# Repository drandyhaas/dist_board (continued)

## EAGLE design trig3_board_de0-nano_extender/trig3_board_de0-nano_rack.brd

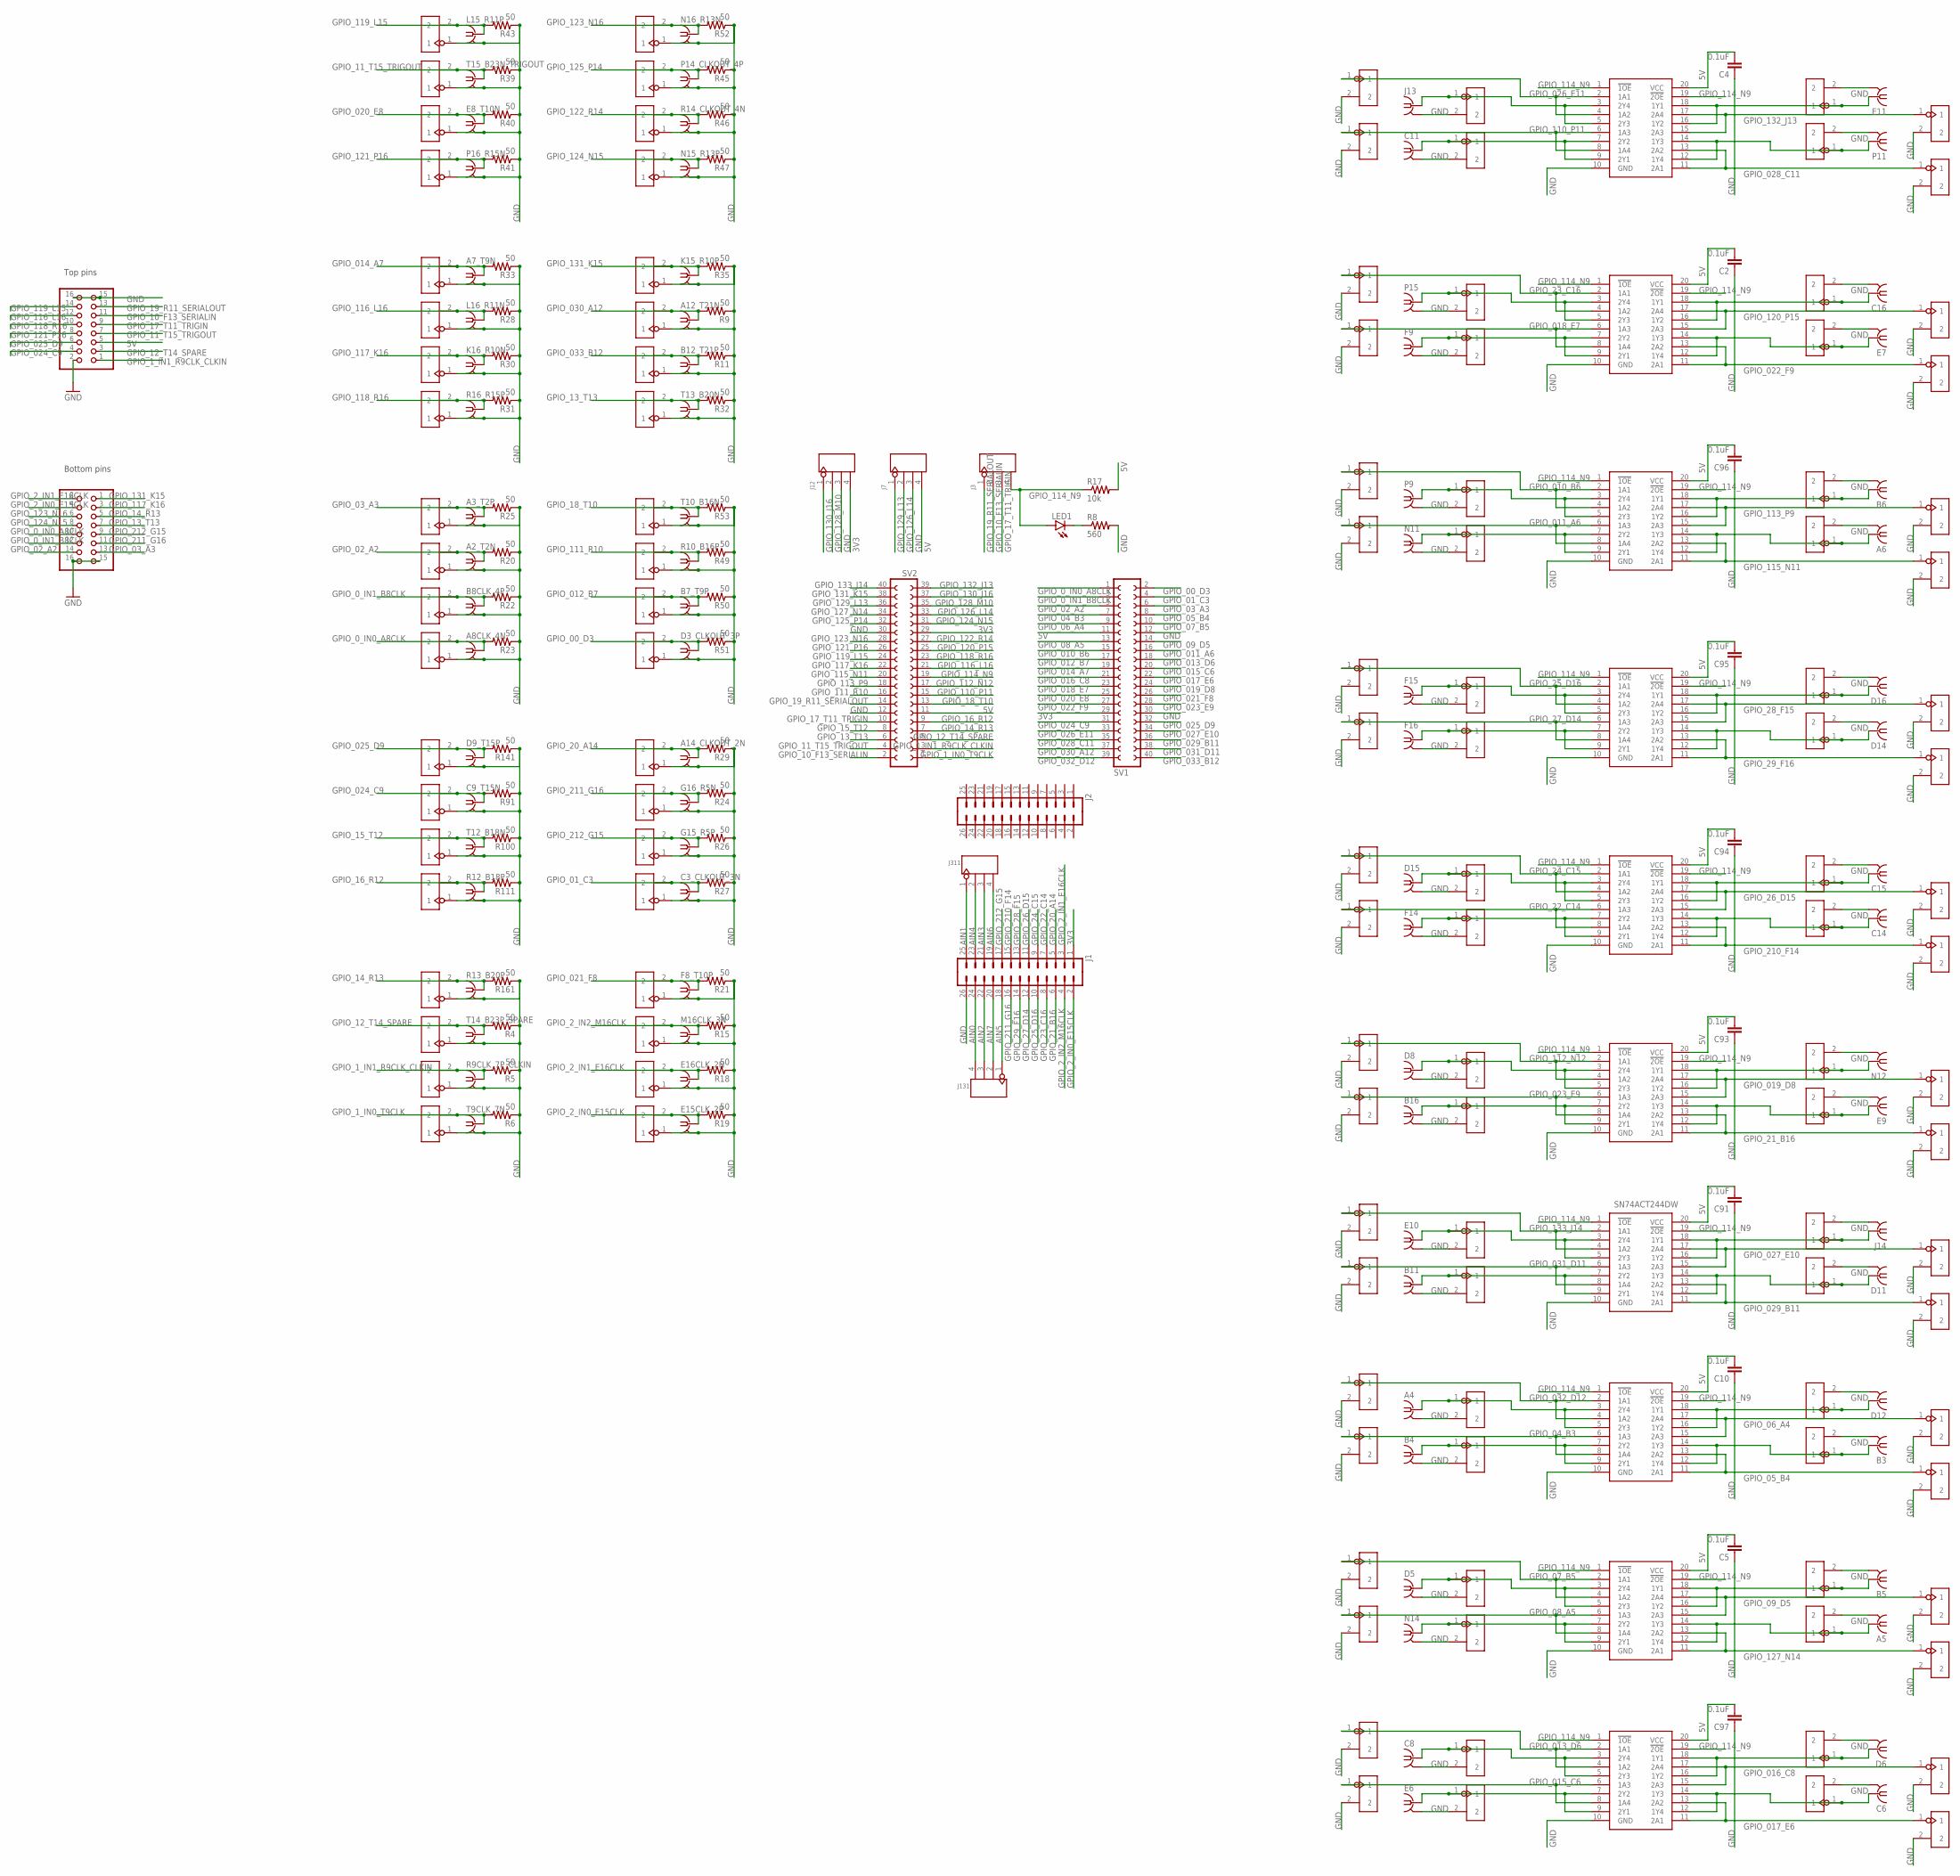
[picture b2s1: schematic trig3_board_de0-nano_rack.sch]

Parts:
A2_T2N, A3_T2P, A4, A5, A6, A7_T9N, A8CLK_4N, A12_T21N, A14_CLKOUT_2N: BU-SMB-V
B3, B4, B5, B6, B7_T9P, B8CLK_4P, B11, B12_T21P, B16: BU-SMB-V
C2, C4, C5, C10, C91, C93, C94, C95, C96, C97: 0.1uF; 0805
C3_CLKOUT_3N, C6, C8, C9_T15N, C11, C14, C15, C16: BU-SMB-V
D3_CLKOUT_3P, D5, D6, D8, D9_T15P, D11, D12, D14, D15, D16: BU-SMB-V
E6, E7, E8_T10N, E9, E10, E11, E15CLK_2P, E16CLK_2N: BU-SMB-V
F8_T10P, F9, F14, F15, F16: BU-SMB-V
G15_R5P, G16_R5N: BU-SMB-V
J1, J2: M13X22X13; 2X13
J3, J7, J12, J131, J311: 4p-2.54; H4-2.54
J4, J5, J6, J8, J9, J10, J11, J15, J16, J17, J18, J22, J23, J24, J25, J28, J29, J30, J31, J32, J33, J34, J35, J36, J37, J38, J39, J40, J41, J42, J43, J48, J49, J50, J51, J52, J53, J54, J55, J141: 2p-2.54; H2-2.54
J13, J14: BU-SMB-V
K15_R10P, K16_R10N: BU-SMB-V
L15_R11P, L16_R11N: BU-SMB-V
LED1: red; CHIP-LED0805
M16CLK_3N: BU-SMB-V
N11, N12, N14, N15_R13P, N16_R13N: BU-SMB-V
OJ1, OJ2, OJ3, OJ4, OJ5, OJ6, OJ7, OJ8, OJ17, OJ18, OJ19, OJ20, OJ21, OJ22, OJ23, OJ24, OJ25, OJ26, OJ27, OJ28, OJ29, OJ30, OJ31, OJ32, OJ33, OJ34, OJ35, OJ36, OJ37, OJ38, OJ39, OJ40, OJ41, OJ42, OJ43, OJ44, OJ45, OJ46, OJ47, OJ48, OJ49, OJ50, OJ51, OJ52, OJ53, OJ54, OJ55, OJ56, OJ57, OJ58, OJ59, OJ60, OJ61, OJ62, OJ63, OJ64, OJ65, OJ66, OJ67, OJ68, OJ69, OJ70, OJ71, OJ72, OJ73, OJ74, OJ75, OJ76, OJ77, OJ78, OJ79, OJ80, OJ89, OJ90, OJ91, OJ92, OJ93, OJ94, OJ95, OJ96: 2p-2.54; H2-2.54
P9, P11, P14_CLKOUT_4P, P15, P16_R15N: BU-SMB-V
PIN_AIN_PWRGND21: 15-91-2160; 2X08/90; MPN 15-91-2160
PIN_ANALOG_21: 15-91-2160; 2X08/90; MPN 15-91-2160
R4, R5, R6, R9, R11, R15, R18, R19, R20, R21, R22, R23, R24, R25, R26, R27, R28, R29, R30, R31, R32, R33, R35, R39, R40, R41, R43, R45, R46, R47, R49, R50, R51, R52, R53, R91, R100, R111, R141, R161: 50; AXIAL-0.3
R8: 560; R0805
R9CLK_7P_CLKIN, R10_B16P, R12_B18P, R13_B20P, R14_CLKOUT_4N, R16_R15P: BU-SMB-V
R17: 10k; R0805
SV1, SV2: FE20-2
T9CLK_7N, T10_B16N, T12_B18N, T13_B20N, T14_B23P_SPARE, T15_B23N_TRIGOUT: BU-SMB-V
VSLUE, VSLUE2, VSLUE3, VSLUE4, VSLUE5, VSLUE6, VSLUE7, VSLUE8, VSLUE9, VSLUE11: SN74ACT244DW; SOIC127P1030X265-20N

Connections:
3V3: J1.1, J12.4, SV1.29, SV2.29
5V: C2.2, C4.2, C5.2, C10.2, C91.2, C93.2, C94.2, C95.2, C96.2, C97.2, J7.4, PIN_ANALOG_21.5, R17.2, SV1.11, SV2.11, VSLUE.20 (VCC), VSLUE2.20 (VCC), VSLUE3.20 (VCC), VSLUE4.20 (VCC), VSLUE5.20 (VCC), VSLUE6.20 (VCC), VSLUE7.20 (VCC), VSLUE8.20 (VCC), VSLUE9.20 (VCC), VSLUE11.20 (VCC)
AIN0: J1.24, J131.4
AIN1: J1.25, J311.1
AIN2: J1.22, J131.3
AIN3: J1.21, J311.3
AIN4: J1.23, J311.2
AIN5: J1.18, J131.1
AIN6: J1.19, J311.4
AIN7: J1.20, J131.2
GND: A2_T2N.2, A2_T2N.3 (2), A2_T2N.4 (2), A2_T2N.5 (2), A3_T2P.2, A3_T2P.3 (2), A3_T2P.4 (2), A3_T2P.5 (2), A4.2, A4.3 (2), A4.4 (2), A4.5 (2), A5.2, A5.3 (2), A5.4 (2), A5.5 (2), A6.2, A6.3 (2), A6.4 (2), A6.5 (2), A7_T9N.2, A7_T9N.3 (2), A7_T9N.4 (2), A7_T9N.5 (2), A8CLK_4N.2, A8CLK_4N.3 (2), A8CLK_4N.4 (2), A8CLK_4N.5 (2), A12_T21N.2, A12_T21N.3 (2), A12_T21N.4 (2), A12_T21N.5 (2), A14_CLKOUT_2N.2, A14_CLKOUT_2N.3 (2), A14_CLKOUT_2N.4 (2), A14_CLKOUT_2N.5 (2), B3.2, B3.3 (2), B3.4 (2), B3.5 (2), B4.2, B4.3 (2), B4.4 (2), B4.5 (2), B5.2, B5.3 (2), B5.4 (2), B5.5 (2), B6.2, B6.3 (2), B6.4 (2), B6.5 (2), B7_T9P.2, B7_T9P.3 (2), B7_T9P.4 (2), B7_T9P.5 (2), B8CLK_4P.2, B8CLK_4P.3 (2), B8CLK_4P.4 (2), B8CLK_4P.5 (2), B11.2, B11.3 (2), B11.4 (2), B11.5 (2), B12_T21P.2, B12_T21P.3 (2), B12_T21P.4 (2), B12_T21P.5 (2), B16.2, B16.3 (2), B16.4 (2), B16.5 (2), C2.1, C3_CLKOUT_3N.2, C3_CLKOUT_3N.3 (2), C3_CLKOUT_3N.4 (2), C3_CLKOUT_3N.5 (2), C4.1, C5.1, C6.2, C6.3 (2), C6.4 (2), C6.5 (2), C8.2, C8.3 (2), C8.4 (2), C8.5 (2), C9_T15N.2, C9_T15N.3 (2), C9_T15N.4 (2), C9_T15N.5 (2), C10.1, C11.2, C11.3 (2), C11.4 (2), C11.5 (2), C14.2, C14.3 (2), C14.4 (2), C14.5 (2), C15.2, C15.3 (2), C15.4 (2), C15.5 (2), C16.2, C16.3 (2), C16.4 (2), C16.5 (2), C91.1, C93.1, C94.1, C95.1, C96.1, C97.1, D3_CLKOUT_3P.2, D3_CLKOUT_3P.3 (2), D3_CLKOUT_3P.4 (2), D3_CLKOUT_3P.5 (2), D5.2, D5.3 (2), D5.4 (2), D5.5 (2), D6.2, D6.3 (2), D6.4 (2), D6.5 (2), D8.2, D8.3 (2), D8.4 (2), D8.5 (2), D9_T15P.2, D9_T15P.3 (2), D9_T15P.4 (2), D9_T15P.5 (2), D11.2, D11.3 (2), D11.4 (2), D11.5 (2), D12.2, D12.3 (2), D12.4 (2), D12.5 (2), D14.2, D14.3 (2), D14.4 (2), D14.5 (2), D15.2, D15.3 (2), D15.4 (2), D15.5 (2), D16.2, D16.3 (2), D16.4 (2), D16.5 (2), E6.2, E6.3 (2), E6.4 (2), E6.5 (2), E7.2, E7.3 (2), E7.4 (2), E7.5 (2), E8_T10N.2, E8_T10N.3 (2), E8_T10N.4 (2), E8_T10N.5 (2), E9.2, E9.3 (2), E9.4 (2), E9.5 (2), E10.2, E10.3 (2), E10.4 (2), E10.5 (2), E11.2, E11.3 (2), E11.4 (2), E11.5 (2), E15CLK_2P.2, E15CLK_2P.3 (2), E15CLK_2P.4 (2), E15CLK_2P.5 (2), E16CLK_2N.2, E16CLK_2N.3 (2), E16CLK_2N.4 (2), E16CLK_2N.5 (2), F8_T10P.2, F8_T10P.3 (2), F8_T10P.4 (2), F8_T10P.5 (2), F9.2, F9.3 (2), F9.4 (2), F9.5 (2), F14.2, F14.3 (2), F14.4 (2), F14.5 (2), F15.2, F15.3 (2), F15.4 (2), F15.5 (2), F16.2, F16.3 (2), F16.4 (2), F16.5 (2), G15_R5P.2, G15_R5P.3 (2), G15_R5P.4 (2), G15_R5P.5 (2), G16_R5N.2, G16_R5N.3 (2), G16_R5N.4 (2), G16_R5N.5 (2), J1.26, J4.1, J5.1, J6.1, J7.3, J8.1, J9.1, J10.1, J11.1, J12.3, J13.2, J13.3 (2), J13.4 (2), J13.5 (2), J14.2, J14.3 (2), J14.4 (2), J14.5 (2), J15.1, J16.1, J17.1, J18.1, J22.1, J23.1, J24.1, J25.1, J28.1, J29.1, J30.1, J31.1, J32.1, J33.1, J34.1, J35.1, J36.1, J37.1, J38.1, J39.1, J40.1, J41.1, J42.1, J43.1, J48.1, J49.1, J50.1, J51.1, J52.1, J53.1, J54.1, J55.1, J141.1, K15_R10P.2, K15_R10P.3 (2), K15_R10P.4 (2), K15_R10P.5 (2), K16_R10N.2, K16_R10N.3 (2), K16_R10N.4 (2), K16_R10N.5 (2), L15_R11P.2, L15_R11P.3 (2), L15_R11P.4 (2), L15_R11P.5 (2), L16_R11N.2, L16_R11N.3 (2), L16_R11N.4 (2), L16_R11N.5 (2), M16CLK_3N.2, M16CLK_3N.3 (2), M16CLK_3N.4 (2), M16CLK_3N.5 (2), N11.2, N11.3 (2), N11.4 (2), N11.5 (2), N12.2, N12.3 (2), N12.4 (2), N12.5 (2), N14.2, N14.3 (2), N14.4 (2), N14.5 (2), N15_R13P.2, N15_R13P.3 (2), N15_R13P.4 (2), N15_R13P.5 (2), N16_R13N.2, N16_R13N.3 (2), N16_R13N.4 (2), N16_R13N.5 (2), OJ1.2, OJ2.2, OJ3.2, OJ4.2, OJ5.2, OJ6.2, OJ7.2, OJ8.2, OJ17.2, OJ18.2, OJ19.2, OJ20.2, OJ21.2, OJ22.2, OJ23.2, OJ24.2, OJ25.2, OJ26.2, OJ27.2, OJ28.2, OJ29.2, OJ30.2, OJ31.2, OJ32.2, OJ33.2, OJ34.2, OJ35.2, OJ36.2, OJ37.2, OJ38.2, OJ39.2, OJ40.2, OJ41.2, OJ42.2, OJ43.2, OJ44.2, OJ45.2, OJ46.2, OJ47.2, OJ48.2, OJ49.2, OJ50.2, OJ51.2, OJ52.2, OJ53.2, OJ54.2, OJ55.2, OJ56.2, OJ57.2, OJ58.2, OJ59.2, OJ60.2, OJ61.2, OJ62.2, OJ63.2, OJ64.2, OJ65.2, OJ66.2, OJ67.2, OJ68.2, OJ69.2, OJ70.2, OJ71.2, OJ72.2, OJ73.2, OJ74.2, OJ75.2, OJ76.2, OJ77.2, OJ78.2, OJ79.2, OJ80.2, OJ89.2, OJ90.2, OJ91.2, OJ92.2, OJ93.2, OJ94.2, OJ95.2, OJ96.2, P9.2, P9.3 (2), P9.4 (2), P9.5 (2), P11.2, P11.3 (2), P11.4 (2), P11.5 (2), P14_CLKOUT_4P.2, P14_CLKOUT_4P.3 (2), P14_CLKOUT_4P.4 (2), P14_CLKOUT_4P.5 (2), P15.2, P15.3 (2), P15.4 (2), P15.5 (2), P16_R15N.2, P16_R15N.3 (2), P16_R15N.4 (2), P16_R15N.5 (2), PIN_AIN_PWRGND21.15, PIN_AIN_PWRGND21.16, PIN_ANALOG_21.2, PIN_ANALOG_21.15, PIN_ANALOG_21.16, R4.P$1 (1), R5.P$1 (1), R6.P$1 (1), R8.2, R9.P$1 (1), R9CLK_7P_CLKIN.2, R9CLK_7P_CLKIN.3 (2), R9CLK_7P_CLKIN.4 (2), R9CLK_7P_CLKIN.5 (2), R10_B16P.2, R10_B16P.3 (2), R10_B16P.4 (2), R10_B16P.5 (2), R11.P$1 (1), R12_B18P.2, R12_B18P.3 (2), R12_B18P.4 (2), R12_B18P.5 (2), R13_B20P.2, R13_B20P.3 (2), R13_B20P.4 (2), R13_B20P.5 (2), R14_CLKOUT_4N.2, R14_CLKOUT_4N.3 (2), R14_CLKOUT_4N.4 (2), R14_CLKOUT_4N.5 (2), R15.P$1 (1), R16_R15P.2, R16_R15P.3 (2), R16_R15P.4 (2), R16_R15P.5 (2), R18.P$1 (1), R19.P$1 (1), R20.P$1 (1), R21.P$1 (1), R22.P$1 (1), R23.P$1 (1), R24.P$1 (1), R25.P$1 (1), R26.P$1 (1), R27.P$1 (1), R28.P$1 (1), R29.P$1 (1), R30.P$1 (1), R31.P$1 (1), R32.P$1 (1), R33.P$1 (1), R35.P$1 (1), R39.P$1 (1), R40.P$1 (1), R41.P$1 (1), R43.P$1 (1), R45.P$1 (1), R46.P$1 (1), R47.P$1 (1), R49.P$1 (1), R50.P$1 (1), R51.P$1 (1), R52.P$1 (1), R53.P$1 (1), R91.P$1 (1), R100.P$1 (1), R111.P$1 (1), R141.P$1 (1), R161.P$1 (1), SV1.12, SV1.30, SV2.12, SV2.30, T9CLK_7N.2, T9CLK_7N.3 (2), T9CLK_7N.4 (2), T9CLK_7N.5 (2), T10_B16N.2, T10_B16N.3 (2), T10_B16N.4 (2), T10_B16N.5 (2), T12_B18N.2, T12_B18N.3 (2), T12_B18N.4 (2), T12_B18N.5 (2), T13_B20N.2, T13_B20N.3 (2), T13_B20N.4 (2), T13_B20N.5 (2), T14_B23P_SPARE.2, T14_B23P_SPARE.3 (2), T14_B23P_SPARE.4 (2), T14_B23P_SPARE.5 (2), T15_B23N_TRIGOUT.2, T15_B23N_TRIGOUT.3 (2), T15_B23N_TRIGOUT.4 (2), T15_B23N_TRIGOUT.5 (2), VSLUE.10 (GND), VSLUE2.10 (GND), VSLUE3.10 (GND), VSLUE4.10 (GND), VSLUE5.10 (GND), VSLUE6.10 (GND), VSLUE7.10 (GND), VSLUE8.10 (GND), VSLUE9.10 (GND), VSLUE11.10 (GND)
GPIO_00_D3: D3_CLKOUT_3P.1, J50.2, R51.P$2 (2), SV1.2
GPIO_0_IN0_A8CLK: A8CLK_4N.1, J24.2, PIN_AIN_PWRGND21.10, R23.P$2 (2), SV1.1
GPIO_0_IN1_B8CLK: B8CLK_4P.1, J23.2, PIN_AIN_PWRGND21.12, R22.P$2 (2), SV1.3
GPIO_01_C3: C3_CLKOUT_3N.1, J30.2, R27.P$2 (2), SV1.4
GPIO_1_IN0_T9CLK: J6.2, R6.P$2 (2), SV2.1, T9CLK_7N.1
GPIO_1_IN1_R9CLK_CLKIN: J5.2, PIN_ANALOG_21.1, R5.P$2 (2), R9CLK_7P_CLKIN.1, SV2.3
GPIO_02_A2: A2_T2N.1, J22.2, PIN_AIN_PWRGND21.14, R20.P$2 (2), SV1.5
GPIO_2_IN0_E15CLK: E15CLK_2P.1, J1.2, J16.2, PIN_AIN_PWRGND21.4, R19.P$2 (2)
GPIO_2_IN1_E16CLK: E16CLK_2N.1, J1.3, J15.2, PIN_AIN_PWRGND21.2, R18.P$2 (2)
GPIO_2_IN2_M16CLK: J1.4, J141.2, M16CLK_3N.1, R15.P$2 (2)
GPIO_03_A3: A3_T2P.1, J25.2, PIN_AIN_PWRGND21.13, R25.P$2 (2), SV1.6
GPIO_04_B3: OJ96.1, SV1.7, VSLUE11.6 (1A3), VSLUE11.8 (1A4)
GPIO_05_B4: OJ94.1, SV1.8, VSLUE11.11 (2A1), VSLUE11.13 (2A2)
GPIO_06_A4: OJ93.1, SV1.9, VSLUE11.15 (2A3), VSLUE11.17 (2A4)
GPIO_07_B5: OJ71.1, SV1.10, VSLUE8.2 (1A1), VSLUE8.4 (1A2)
GPIO_08_A5: OJ72.1, SV1.13, VSLUE8.6 (1A3), VSLUE8.8 (1A4)
GPIO_09_D5: OJ69.1, SV1.14, VSLUE8.15 (2A3), VSLUE8.17 (2A4)
GPIO_010_B6: OJ47.1, SV1.15, VSLUE5.2 (1A1), VSLUE5.4 (1A2)
GPIO_10_F13_SERIALIN: J3.2, PIN_ANALOG_21.11, SV2.2
GPIO_011_A6: OJ48.1, SV1.16, VSLUE5.6 (1A3), VSLUE5.8 (1A4)
GPIO_11_T15_TRIGOUT: J40.2, PIN_ANALOG_21.7, R39.P$2 (2), SV2.4, T15_B23N_TRIGOUT.1
GPIO_012_B7: B7_T9P.1, J49.2, R50.P$2 (2), SV1.17
GPIO_12_T14_SPARE: J4.2, PIN_ANALOG_21.3, R4.P$2 (2), SV2.5, T14_B23P_SPARE.1
GPIO_013_D6: OJ55.1, SV1.18, VSLUE6.2 (1A1), VSLUE6.4 (1A2)
GPIO_13_T13: J38.2, PIN_AIN_PWRGND21.7, R32.P$2 (2), SV2.6, T13_B20N.1
GPIO_014_A7: A7_T9N.1, J35.2, R33.P$2 (2), SV1.19
GPIO_14_R13: J17.2, PIN_AIN_PWRGND21.5, R13_B20P.1, R161.P$2 (2), SV2.7
GPIO_015_C6: OJ56.1, SV1.20, VSLUE6.6 (1A3), VSLUE6.8 (1A4)
GPIO_15_T12: J9.2, R100.P$2 (2), SV2.8, T12_B18N.1
GPIO_016_C8: OJ53.1, SV1.21, VSLUE6.15 (2A3), VSLUE6.17 (2A4)
GPIO_16_R12: J10.2, R12_B18P.1, R111.P$2 (2), SV2.9
GPIO_017_E6: OJ54.1, SV1.22, VSLUE6.11 (2A1), VSLUE6.13 (2A2)
GPIO_17_T11_TRIGIN: J3.3, PIN_ANALOG_21.9, SV2.10
GPIO_018_E7: OJ64.1, SV1.23, VSLUE7.6 (1A3), VSLUE7.8 (1A4)
GPIO_18_T10: J51.2, R53.P$2 (2), SV2.13, T10_B16N.1
GPIO_019_D8: OJ21.1, SV1.24, VSLUE2.15 (2A3), VSLUE2.17 (2A4)
GPIO_19_R11_SERIALOUT: J3.1, PIN_ANALOG_21.13, SV2.14
GPIO_20_A14: A14_CLKOUT_2N.1, J1.5, J31.2, R29.P$2 (2)
GPIO_020_E8: E8_T10N.1, J41.2, R40.P$2 (2), SV1.25
GPIO_21_B16: J1.6, OJ22.1, VSLUE2.11 (2A1), VSLUE2.13 (2A2)
GPIO_021_F8: F8_T10P.1, J18.2, R21.P$2 (2), SV1.26
GPIO_22_C14: J1.7, OJ32.1, VSLUE3.6 (1A3), VSLUE3.8 (1A4)
GPIO_022_F9: OJ62.1, SV1.27, VSLUE7.11 (2A1), VSLUE7.13 (2A2)
GPIO_23_C16: J1.8, OJ63.1, VSLUE7.2 (1A1), VSLUE7.4 (1A2)
GPIO_023_E9: OJ24.1, SV1.28, VSLUE2.6 (1A3), VSLUE2.8 (1A4)
GPIO_024_C9: C9_T15N.1, J8.2, PIN_ANALOG_21.4, R91.P$2 (2), SV1.31
GPIO_24_C15: J1.9, OJ31.1, VSLUE3.2 (1A1), VSLUE3.4 (1A2)
GPIO_025_D9: D9_T15P.1, J11.2, PIN_ANALOG_21.6, R141.P$2 (2), SV1.32
GPIO_25_D16: J1.10, OJ39.1, VSLUE4.2 (1A1), VSLUE4.4 (1A2)
GPIO_26_D15: J1.11, OJ29.1, VSLUE3.15 (2A3), VSLUE3.17 (2A4)
GPIO_026_E11: OJ79.1, SV1.33, VSLUE9.2 (1A1), VSLUE9.4 (1A2)
GPIO_27_D14: J1.12, OJ40.1, VSLUE4.6 (1A3), VSLUE4.8 (1A4)
GPIO_027_E10: OJ5.1, SV1.34, VSLUE.15 (2A3), VSLUE.17 (2A4)
GPIO_028_C11: OJ78.1, SV1.35, VSLUE9.11 (2A1), VSLUE9.13 (2A2)
GPIO_28_F15: J1.13, OJ37.1, VSLUE4.15 (2A3), VSLUE4.17 (2A4)
GPIO_029_B11: OJ6.1, SV1.36, VSLUE.11 (2A1), VSLUE.13 (2A2)
GPIO_29_F16: J1.14, OJ38.1, VSLUE4.11 (2A1), VSLUE4.13 (2A2)
GPIO_030_A12: A12_T21N.1, J36.2, R9.P$2 (2), SV1.37
GPIO_031_D11: OJ8.1, SV1.38, VSLUE.6 (1A3), VSLUE.8 (1A4)
GPIO_032_D12: OJ95.1, SV1.39, VSLUE11.2 (1A1), VSLUE11.4 (1A2)
GPIO_033_B12: B12_T21P.1, J37.2, R11.P$2 (2), SV1.40
GPIO_110_P11: OJ80.1, SV2.15, VSLUE9.6 (1A3), VSLUE9.8 (1A4)
GPIO_111_R10: J48.2, R10_B16P.1, R49.P$2 (2), SV2.16
GPIO_112_N12: OJ23.1, SV2.17, VSLUE2.2 (1A1), VSLUE2.4 (1A2)
GPIO_113_P9: OJ45.1, SV2.18, VSLUE5.15 (2A3), VSLUE5.17 (2A4)
GPIO_114_N9: J3.4, LED1.A, R17.1, SV2.19, VSLUE.1 (!1OE), VSLUE.19 (!2OE), VSLUE2.1 (!1OE), VSLUE2.19 (!2OE), VSLUE3.1 (!1OE), VSLUE3.19 (!2OE), VSLUE4.1 (!1OE), VSLUE4.19 (!2OE), VSLUE5.1 (!1OE), VSLUE5.19 (!2OE), VSLUE6.1 (!1OE), VSLUE6.19 (!2OE), VSLUE7.1 (!1OE), VSLUE7.19 (!2OE), VSLUE8.1 (!1OE), VSLUE8.19 (!2OE), VSLUE9.1 (!1OE), VSLUE9.19 (!2OE), VSLUE11.1 (!1OE), VSLUE11.19 (!2OE)
GPIO_115_N11: OJ46.1, SV2.20, VSLUE5.11 (2A1), VSLUE5.13 (2A2)
GPIO_116_L16: J32.2, L16_R11N.1, PIN_ANALOG_21.12, R28.P$2 (2), SV2.21
GPIO_117_K16: J33.2, K16_R10N.1, PIN_AIN_PWRGND21.3, R30.P$2 (2), SV2.22
GPIO_118_R16: J34.2, PIN_ANALOG_21.10, R16_R15P.1, R31.P$2 (2), SV2.23
GPIO_119_L15: J43.2, L15_R11P.1, PIN_ANALOG_21.14, R43.P$2 (2), SV2.24
GPIO_120_P15: OJ61.1, SV2.25, VSLUE7.15 (2A3), VSLUE7.17 (2A4)
GPIO_121_P16: J42.2, P16_R15N.1, PIN_ANALOG_21.8, R41.P$2 (2), SV2.26
GPIO_122_R14: J53.2, R14_CLKOUT_4N.1, R46.P$2 (2), SV2.27
GPIO_123_N16: J55.2, N16_R13N.1, PIN_AIN_PWRGND21.6, R52.P$2 (2), SV2.28
GPIO_124_N15: J54.2, N15_R13P.1, PIN_AIN_PWRGND21.8, R47.P$2 (2), SV2.31
GPIO_125_P14: J52.2, P14_CLKOUT_4P.1, R45.P$2 (2), SV2.32
GPIO_126_L14: J7.2, SV2.33
GPIO_127_N14: OJ70.1, SV2.34, VSLUE8.11 (2A1), VSLUE8.13 (2A2)
GPIO_128_M10: J12.2, SV2.35
GPIO_129_L13: J7.1, SV2.36
GPIO_130_J16: J12.1, SV2.37
GPIO_131_K15: J39.2, K15_R10P.1, PIN_AIN_PWRGND21.1, R35.P$2 (2), SV2.38
GPIO_132_J13: OJ77.1, SV2.39, VSLUE9.15 (2A3), VSLUE9.17 (2A4)
GPIO_133_J14: OJ7.1, SV2.40, VSLUE.2 (1A1), VSLUE.4 (1A2)
GPIO_210_F14: J1.15, OJ30.1, VSLUE3.11 (2A1), VSLUE3.13 (2A2)
GPIO_211_G16: G16_R5N.1, J1.16, J28.2, PIN_AIN_PWRGND21.11, R24.P$2 (2)
GPIO_212_G15: G15_R5P.1, J1.17, J29.2, PIN_AIN_PWRGND21.9, R26.P$2 (2)
LED1R: LED1.C, R8.1
OUT1: J14.1, OJ1.1, VSLUE.16 (1Y2), VSLUE.18 (1Y1)
OUT2: D11.1, OJ2.1, VSLUE.12 (1Y4), VSLUE.14 (1Y3)
OUT3: B11.1, OJ3.1, VSLUE.7 (2Y2), VSLUE.9 (2Y1)
OUT4: E10.1, OJ4.1, VSLUE.3 (2Y4), VSLUE.5 (2Y3)
OUT9: N12.1, OJ20.1, VSLUE2.16 (1Y2), VSLUE2.18 (1Y1)
OUT10: E9.1, OJ19.1, VSLUE2.12 (1Y4), VSLUE2.14 (1Y3)
OUT11: D8.1, OJ17.1, VSLUE2.3 (2Y4), VSLUE2.5 (2Y3)
OUT12: B16.1, OJ18.1, VSLUE2.7 (2Y2), VSLUE2.9 (2Y1)
OUT13: C15.1, OJ28.1, VSLUE3.16 (1Y2), VSLUE3.18 (1Y1)
OUT14: C14.1, OJ27.1, VSLUE3.12 (1Y4), VSLUE3.14 (1Y3)
OUT15: D15.1, OJ25.1, VSLUE3.3 (2Y4), VSLUE3.5 (2Y3)
OUT16: F14.1, OJ26.1, VSLUE3.7 (2Y2), VSLUE3.9 (2Y1)
OUT17: D16.1, OJ36.1, VSLUE4.16 (1Y2), VSLUE4.18 (1Y1)
OUT18: D14.1, OJ35.1, VSLUE4.12 (1Y4), VSLUE4.14 (1Y3)
OUT19: F15.1, OJ33.1, VSLUE4.3 (2Y4), VSLUE4.5 (2Y3)
OUT20: F16.1, OJ34.1, VSLUE4.7 (2Y2), VSLUE4.9 (2Y1)
OUT21: B6.1, OJ44.1, VSLUE5.16 (1Y2), VSLUE5.18 (1Y1)
OUT22: A6.1, OJ43.1, VSLUE5.12 (1Y4), VSLUE5.14 (1Y3)
OUT23: OJ41.1, P9.1, VSLUE5.3 (2Y4), VSLUE5.5 (2Y3)
OUT24: N11.1, OJ42.1, VSLUE5.7 (2Y2), VSLUE5.9 (2Y1)
OUT25: D6.1, OJ52.1, VSLUE6.16 (1Y2), VSLUE6.18 (1Y1)
OUT26: C6.1, OJ51.1, VSLUE6.12 (1Y4), VSLUE6.14 (1Y3)
OUT27: C8.1, OJ49.1, VSLUE6.3 (2Y4), VSLUE6.5 (2Y3)
OUT28: E6.1, OJ50.1, VSLUE6.7 (2Y2), VSLUE6.9 (2Y1)
OUT29: C16.1, OJ60.1, VSLUE7.16 (1Y2), VSLUE7.18 (1Y1)
OUT30: E7.1, OJ59.1, VSLUE7.12 (1Y4), VSLUE7.14 (1Y3)
OUT31: OJ57.1, P15.1, VSLUE7.3 (2Y4), VSLUE7.5 (2Y3)
OUT32: F9.1, OJ58.1, VSLUE7.7 (2Y2), VSLUE7.9 (2Y1)
OUT33: B5.1, OJ68.1, VSLUE8.16 (1Y2), VSLUE8.18 (1Y1)
OUT34: A5.1, OJ67.1, VSLUE8.12 (1Y4), VSLUE8.14 (1Y3)
OUT35: D5.1, OJ65.1, VSLUE8.3 (2Y4), VSLUE8.5 (2Y3)
OUT36: N14.1, OJ66.1, VSLUE8.7 (2Y2), VSLUE8.9 (2Y1)
OUT37: E11.1, OJ76.1, VSLUE9.16 (1Y2), VSLUE9.18 (1Y1)
OUT38: OJ75.1, P11.1, VSLUE9.12 (1Y4), VSLUE9.14 (1Y3)
OUT39: J13.1, OJ73.1, VSLUE9.3 (2Y4), VSLUE9.5 (2Y3)
OUT40: C11.1, OJ74.1, VSLUE9.7 (2Y2), VSLUE9.9 (2Y1)
OUT45: D12.1, OJ92.1, VSLUE11.16 (1Y2), VSLUE11.18 (1Y1)
OUT46: B3.1, OJ91.1, VSLUE11.12 (1Y4), VSLUE11.14 (1Y3)
OUT47: A4.1, OJ89.1, VSLUE11.3 (2Y4), VSLUE11.5 (2Y3)
OUT48: B4.1, OJ90.1, VSLUE11.7 (2Y2), VSLUE11.9 (2Y1)

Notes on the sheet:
Top pins
Bottom pins

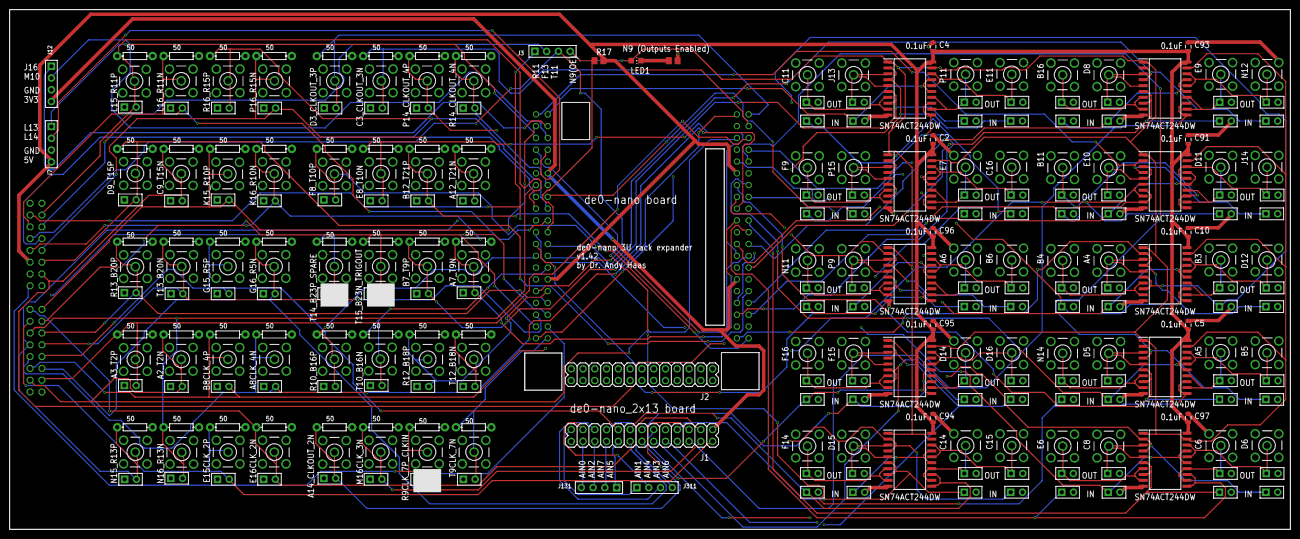
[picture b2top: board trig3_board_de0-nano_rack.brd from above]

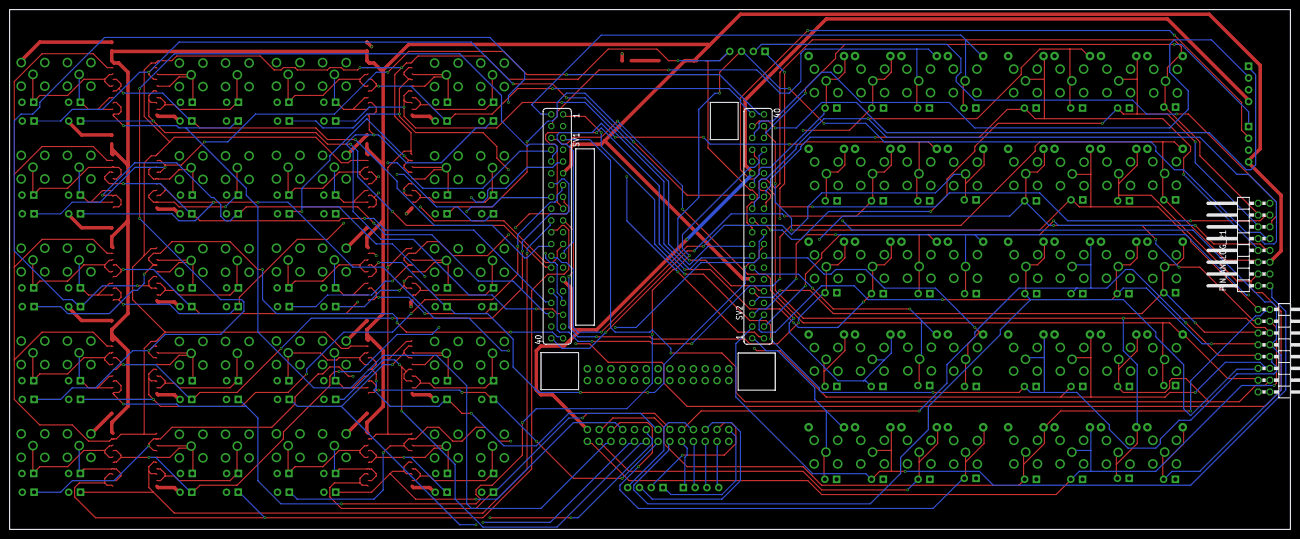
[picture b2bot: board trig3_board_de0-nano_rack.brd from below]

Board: 4 copper layers, 276.0 x 112.0 mm, 274 parts (4 on the bottom side), 140 nets.

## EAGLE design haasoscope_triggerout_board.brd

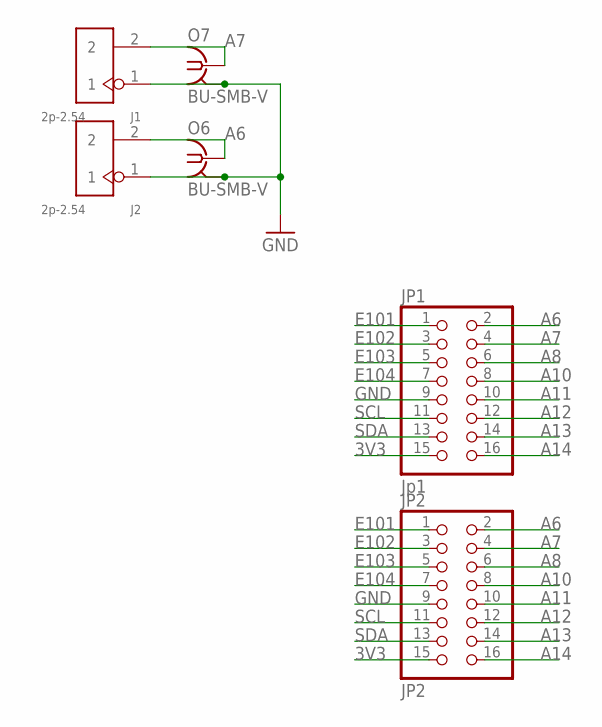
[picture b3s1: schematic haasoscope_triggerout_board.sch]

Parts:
J1, J2: 2p-2.54; H2-2.54
JP1: Jp1; 2X08
JP2: JP2; 2X08
O6, O7: BU-SMB-V

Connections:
3V3: JP1.15, JP2.15
A6: J2.2, JP1.2, JP2.2, O6.1
A7: J1.2, JP1.4, JP2.4, O7.1
A8: JP1.6, JP2.6
A10: JP1.8, JP2.8
A11: JP1.10, JP2.10
A12: JP1.12, JP2.12
A13: JP1.14, JP2.14
A14: JP1.16, JP2.16
E101: JP1.1, JP2.1
E102: JP1.3, JP2.3
E103: JP1.5, JP2.5
E104: JP1.7, JP2.7
GND: J1.1, J2.1, JP1.9, JP2.9, O6.2, O6.3 (2), O6.4 (2), O6.5 (2), O7.2, O7.3 (2), O7.4 (2), O7.5 (2)
SCL: JP1.11, JP2.11
SDA: JP1.13, JP2.13

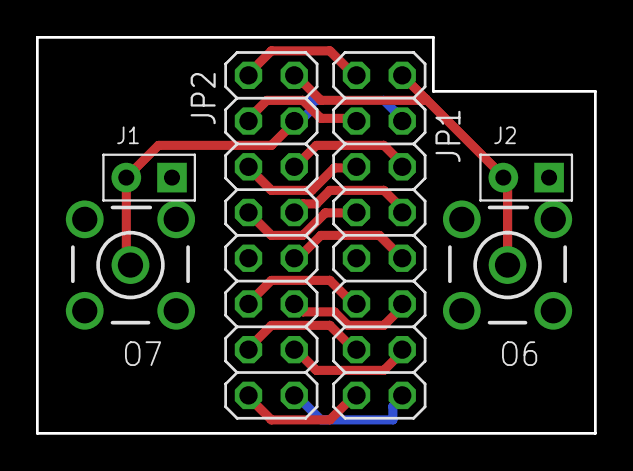
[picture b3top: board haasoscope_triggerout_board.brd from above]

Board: 2 copper layers, 31.0 x 22.0 mm, 6 parts (0 on the bottom side), 16 nets.

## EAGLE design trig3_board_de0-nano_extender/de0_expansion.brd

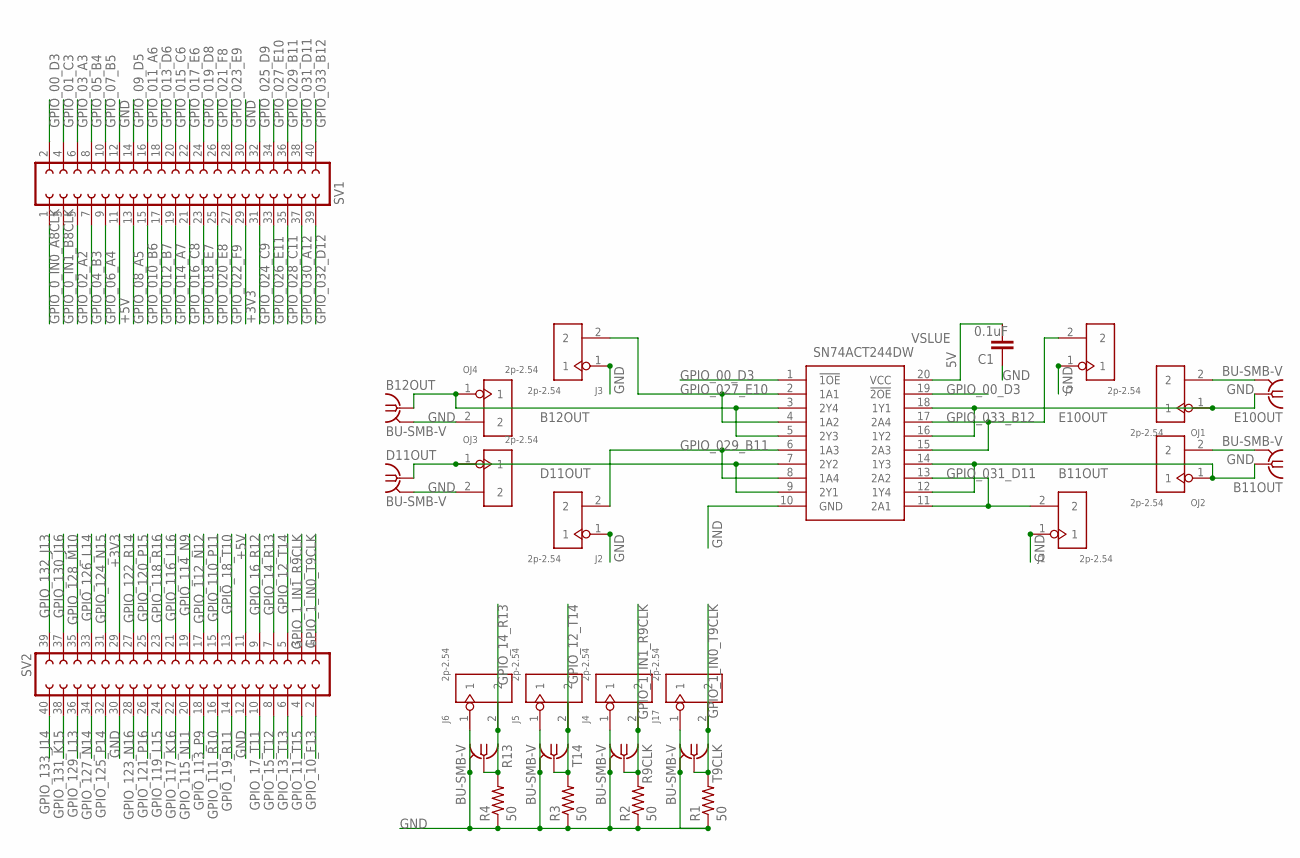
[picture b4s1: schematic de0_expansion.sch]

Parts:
B11OUT, B12OUT: BU-SMB-V
C1: 0.1uF; 0805
D11OUT: BU-SMB-V
E10OUT: BU-SMB-V
J1, J2, J3, J4, J5, J6, J7, J17: 2p-2.54; H2-2.54
OJ1, OJ2, OJ3, OJ4: 2p-2.54; H2-2.54
R1, R2, R3, R4: 50; AXIAL-0.3
R9CLK, R13: BU-SMB-V
SV1, SV2: FE20-2
T9CLK, T14: BU-SMB-V
VSLUE: SN74ACT244DW; SOIC127P1030X265-20N

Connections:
5V: C1.2, VSLUE.20 (VCC)
+3V3: SV1.29, SV2.29
+5V: SV1.11, SV2.11
B11OUT: B11OUT.1, OJ2.1, VSLUE.12 (1Y4), VSLUE.14 (1Y3)
B12OUT: B12OUT.1, OJ4.1, VSLUE.3 (2Y4), VSLUE.5 (2Y3)
D11OUT: D11OUT.1, OJ3.1, VSLUE.7 (2Y2), VSLUE.9 (2Y1)
E10OUT: E10OUT.1, OJ1.1, VSLUE.16 (1Y2), VSLUE.18 (1Y1)
GND: B11OUT.2, B11OUT.3 (2), B11OUT.4 (2), B11OUT.5 (2), B12OUT.2, B12OUT.3 (2), B12OUT.4 (2), B12OUT.5 (2), C1.1, D11OUT.2, D11OUT.3 (2), D11OUT.4 (2), D11OUT.5 (2), E10OUT.2, E10OUT.3 (2), E10OUT.4 (2), E10OUT.5 (2), J1.1, J2.1, J3.1, J4.1, J5.1, J6.1, J7.1, J17.1, OJ1.2, OJ2.2, OJ3.2, OJ4.2, R1.P$1 (1), R2.P$1 (1), R3.P$1 (1), R4.P$1 (1), R9CLK.2, R9CLK.3 (2), R9CLK.4 (2), R9CLK.5 (2), R13.2, R13.3 (2), R13.4 (2), R13.5 (2), SV1.12, SV1.30, SV2.12, SV2.30, T9CLK.2, T9CLK.3 (2), T9CLK.4 (2), T9CLK.5 (2), T14.2, T14.3 (2), T14.4 (2), T14.5 (2), VSLUE.10 (GND)
GPIO_00_D3: SV1.2, VSLUE.1 (!1OE), VSLUE.19 (!2OE)
GPIO_0_IN0_A8CLK: SV1.1
GPIO_0_IN1_B8CLK: SV1.3
GPIO_01_C3: SV1.4
GPIO_1_IN0_T9CLK: J17.2, R1.P$2 (2), SV2.1, T9CLK.1
GPIO_1_IN1_R9CLK: J4.2, R2.P$2 (2), R9CLK.1, SV2.3
GPIO_02_A2: SV1.5
GPIO_03_A3: SV1.6
GPIO_04_B3: SV1.7
GPIO_05_B4: SV1.8
GPIO_06_A4: SV1.9
GPIO_07_B5: SV1.10
GPIO_08_A5: SV1.13
GPIO_09_D5: SV1.14
GPIO_010_B6: SV1.15
GPIO_10_F13: SV2.2
GPIO_011_A6: SV1.16
GPIO_11_T15: SV2.4
GPIO_012_B7: SV1.17
GPIO_12_T14: J5.2, R3.P$2 (2), SV2.5, T14.1
GPIO_013_D6: SV1.18
GPIO_13_T13: SV2.6
GPIO_014_A7: SV1.19
GPIO_14_R13: J6.2, R4.P$2 (2), R13.1, SV2.7
GPIO_015_C6: SV1.20
GPIO_15_T12: SV2.8
GPIO_016_C8: SV1.21
GPIO_16_R12: SV2.9
GPIO_017_E6: SV1.22
GPIO_17_T11: SV2.10
GPIO_018_E7: SV1.23
GPIO_18_T10: SV2.13
GPIO_019_D8: SV1.24
GPIO_19_R11: SV2.14
GPIO_020_E8: SV1.25
GPIO_021_F8: SV1.26
GPIO_022_F9: SV1.27
GPIO_023_E9: SV1.28
GPIO_024_C9: SV1.31
GPIO_025_D9: SV1.32
GPIO_026_E11: SV1.33
GPIO_027_E10: J3.2, SV1.34, VSLUE.2 (1A1), VSLUE.4 (1A2)
GPIO_028_C11: SV1.35
GPIO_029_B11: J2.2, SV1.36, VSLUE.6 (1A3), VSLUE.8 (1A4)
GPIO_030_A12: SV1.37
GPIO_031_D11: J1.2, SV1.38, VSLUE.11 (2A1), VSLUE.13 (2A2)
GPIO_032_D12: SV1.39
GPIO_033_B12: J7.2, SV1.40, VSLUE.15 (2A3), VSLUE.17 (2A4)
GPIO_110_P11: SV2.15
GPIO_111_R10: SV2.16
GPIO_112_N12: SV2.17
GPIO_113_P9: SV2.18
GPIO_114_N9: SV2.19
GPIO_115_N11: SV2.20
GPIO_116_L16: SV2.21
GPIO_117_K16: SV2.22
GPIO_118_R16: SV2.23
GPIO_119_L15: SV2.24
GPIO_120_P15: SV2.25
GPIO_121_P16: SV2.26
GPIO_122_R14: SV2.27
GPIO_123_N16: SV2.28
GPIO_124_N15: SV2.31
GPIO_125_P14: SV2.32
GPIO_126_L14: SV2.33
GPIO_127_N14: SV2.34
GPIO_128_M10: SV2.35
GPIO_129_L13: SV2.36
GPIO_130_J16: SV2.37
GPIO_131_K15: SV2.38
GPIO_132_J13: SV2.39
GPIO_133_J14: SV2.40

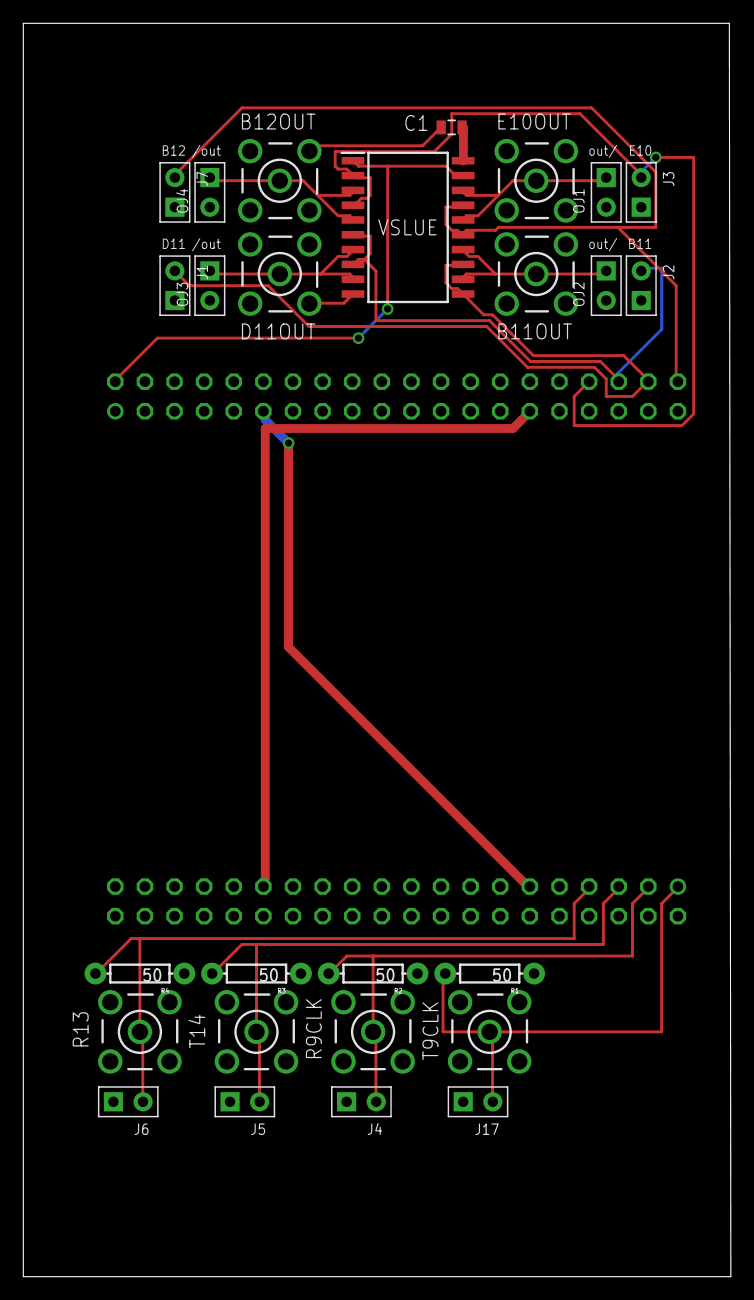
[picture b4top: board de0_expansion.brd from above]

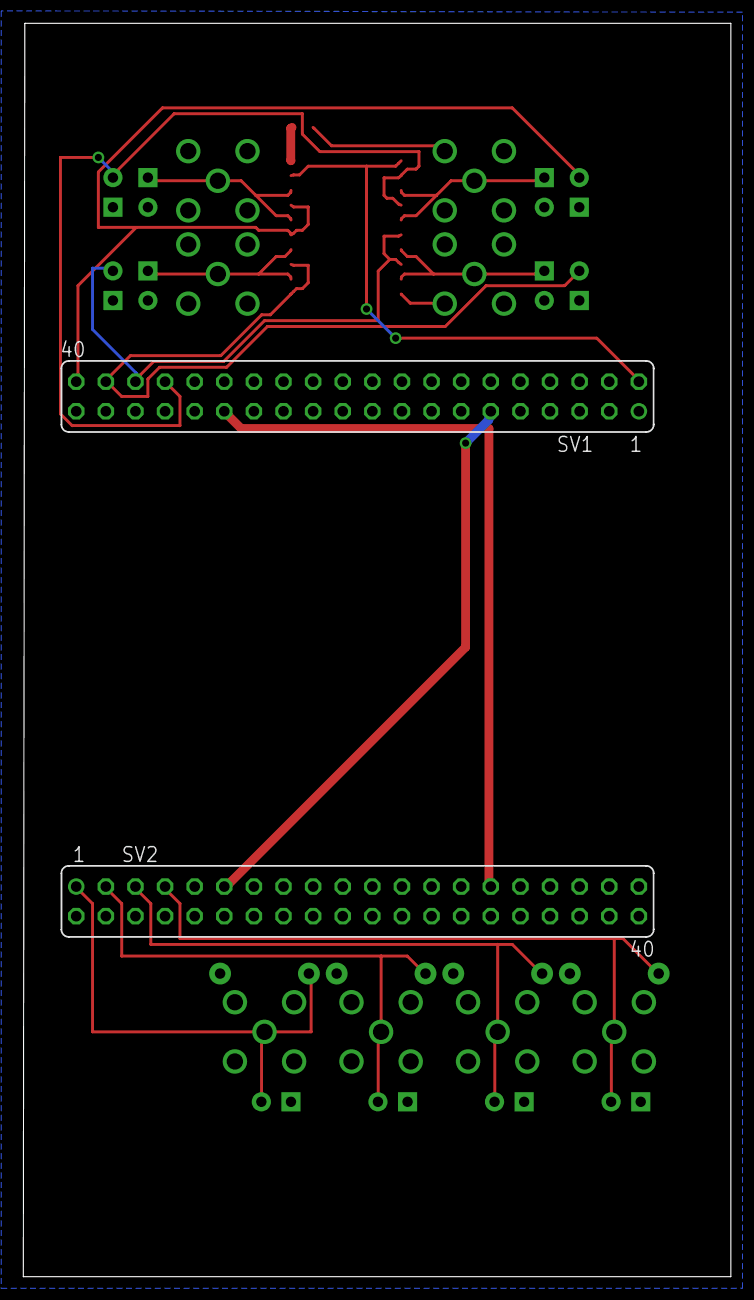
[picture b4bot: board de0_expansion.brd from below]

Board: 2 copper layers, 60.7 x 107.5 mm, 28 parts (2 on the bottom side), 17 nets.
